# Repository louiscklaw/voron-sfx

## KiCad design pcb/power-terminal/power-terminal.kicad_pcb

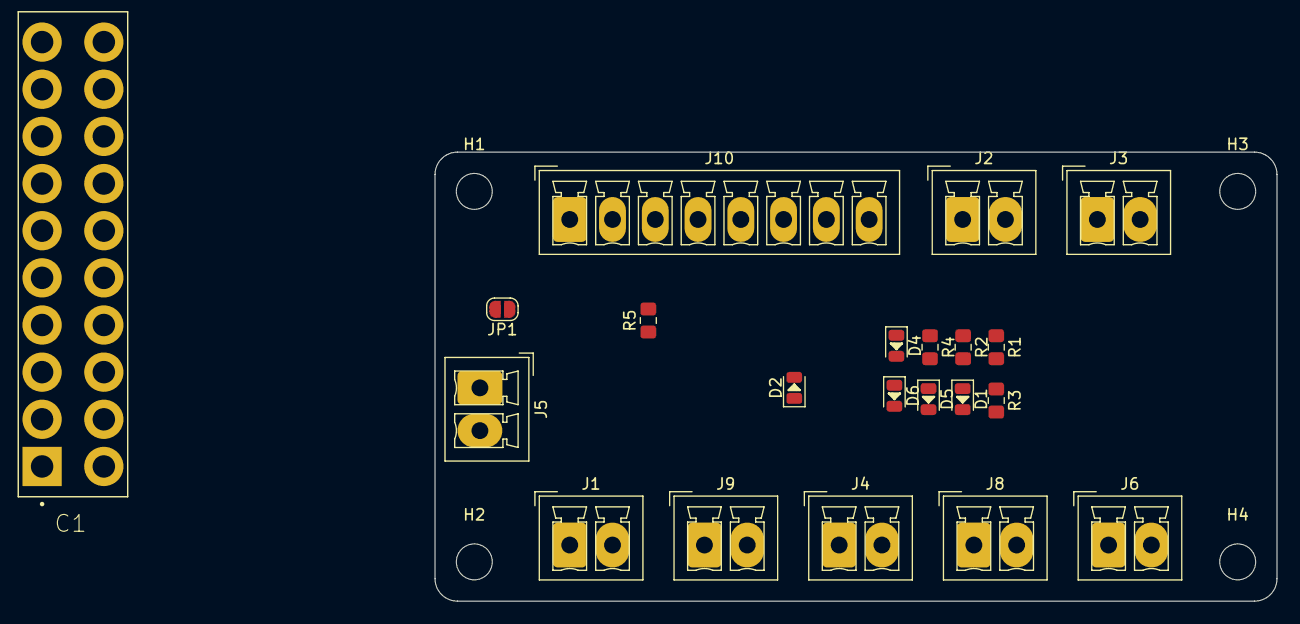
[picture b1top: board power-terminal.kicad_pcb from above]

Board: 2 copper layers, 75.0 x 40.0 mm, 25 parts (0 on the bottom side), 12 nets, no tracks yet.

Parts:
C1: ATX_20_pin_power_connector; ATX_20_pin_power_connector_vertical
D1: 3V3_HEALTHY; LED_0805_2012Metric
D2, D4: +5V_HEALTHY; LED_0805_2012Metric
D5: +12V_HEALTHY; LED_0805_2012Metric
D6: PS_ON_STATUS; LED_0805_2012Metric
H1, H2, H3, H4: MountingHole; MountingHole_3.2mm_M3,rpi_like
J1: +5V_ALWAYS_ON; PhoenixContact_MCV_1,5_2-G-3.81_1x02_P3.81mm_Vertical
J2: +PS_ON; PhoenixContact_MCV_1,5_2-G-3.81_1x02_P3.81mm_Vertical
J3: PWR_OK; PhoenixContact_MCV_1,5_2-G-3.81_1x02_P3.81mm_Vertical
J4, J9: +5V; PhoenixContact_MCV_1,5_2-G-3.81_1x02_P3.81mm_Vertical
J5: +3V3; PhoenixContact_MCV_1,5_2-G-3.81_1x02_P3.81mm_Vertical
J6, J8: +12V; PhoenixContact_MCV_1,5_2-G-3.81_1x02_P3.81mm_Vertical
J10: FROM-PSU; PhoenixContact_MCV_1,5_8-G-3.81_1x08_P3.81mm_Vertical
JP1: ALWAYS_ON; SolderJumper-2_P1.3mm_Open_RoundedPad1.0x1.5mm
R1, R2, R3, R4, R5: R103,0805; R_0805_2012Metric_Pad1.15x1.40mm_HandSolder

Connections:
/+3V3: J5.1, J10.2, R1.2
/+5V: J4.1, J9.1, J10.3, R2.2
/+5V_SB: J10.6, R5.2
/+12V: J6.1, J8.1, J10.4, R3.2
/PS_ON: J2.1, J10.8, JP1.2
/PW_OK: J3.1, J10.7, R4.2
GND: D1.1, D2.1, D4.1, D5.1, D6.1, J1.2, J2.2, J3.2, J4.2, J5.2, J6.2, J8.2, J9.2, J10.1, JP1.1
unnamed: D1.2, R1.1
unnamed: D2.2, R5.1
unnamed: D4.2, R2.1
unnamed: D5.2, R3.1
unnamed: D6.2, R4.1

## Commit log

2020-02-08 init commit,
2020-02-08 update,
2020-02-08 update drawing,
2020-02-08 update for sfx mounts,
2020-04-22 add files,
2020-04-22 add more files,
2020-04-25 update for travis merger,
2020-04-25 update for filament holder,
2020-04-25 update for filament-tube-cover,
2020-04-25 update for cable-clip,
2020-04-25 add z-drive cover,
2020-04-25 update travis token,
2020-04-26 update for testing z-idlers,
2020-04-26 testing update z-idlers,
2020-04-26 init change and test,
2020-04-26 udpate,
2020-04-28 content: add references,
2020-04-29 update with 2020 profile,
2020-05-15 ci: upcate travis.yml and new credentials,
